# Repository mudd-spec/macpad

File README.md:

# macpad

The macpad is a 9 key macropad/keyboard with 2 EC11 style rotary encoders.

## Features:
- Sandwich style mount - 3D printable, BUT you need screws and heatset inserts
- EC11 Rotary encoders for rotational action AND they serve as switches/keys
- 9 fully programmable keys in a matrix

## CAD Model:
4 heatset inserts and 4 M3 screws are used to keep everything together

The model consists of a bottom case, a plate, and a bracket for the top, so the key switches themselves are less exposed.

There are also optional rotary encoder dials.

## PCB / Schematic
The PCB as well as the schematic is pictured below:

Schematic

PCB

## Firmware Overview
This hackpad uses [QMK](https://qmk.fm/) firmware for everything. 

- caution: the current keybinds are not advised for actual use

## BOM:
Here is everything needed to make the macpad

- 9x Cherry MX Switches
- 9x DSA Keycaps
- 4x M3x5x4 Heatset inserts
- 4X M3x12mm SHCS Bolts
- 11x 1N4148 DO-35 Diodes.
- 2x EC11 Rotary Encoder
- 1x XIAO RP2040
- 1x Case (3 3D printed parts)
- 2x Rotary Encoder Dials (2 3D printed parts)
- 1x PCB

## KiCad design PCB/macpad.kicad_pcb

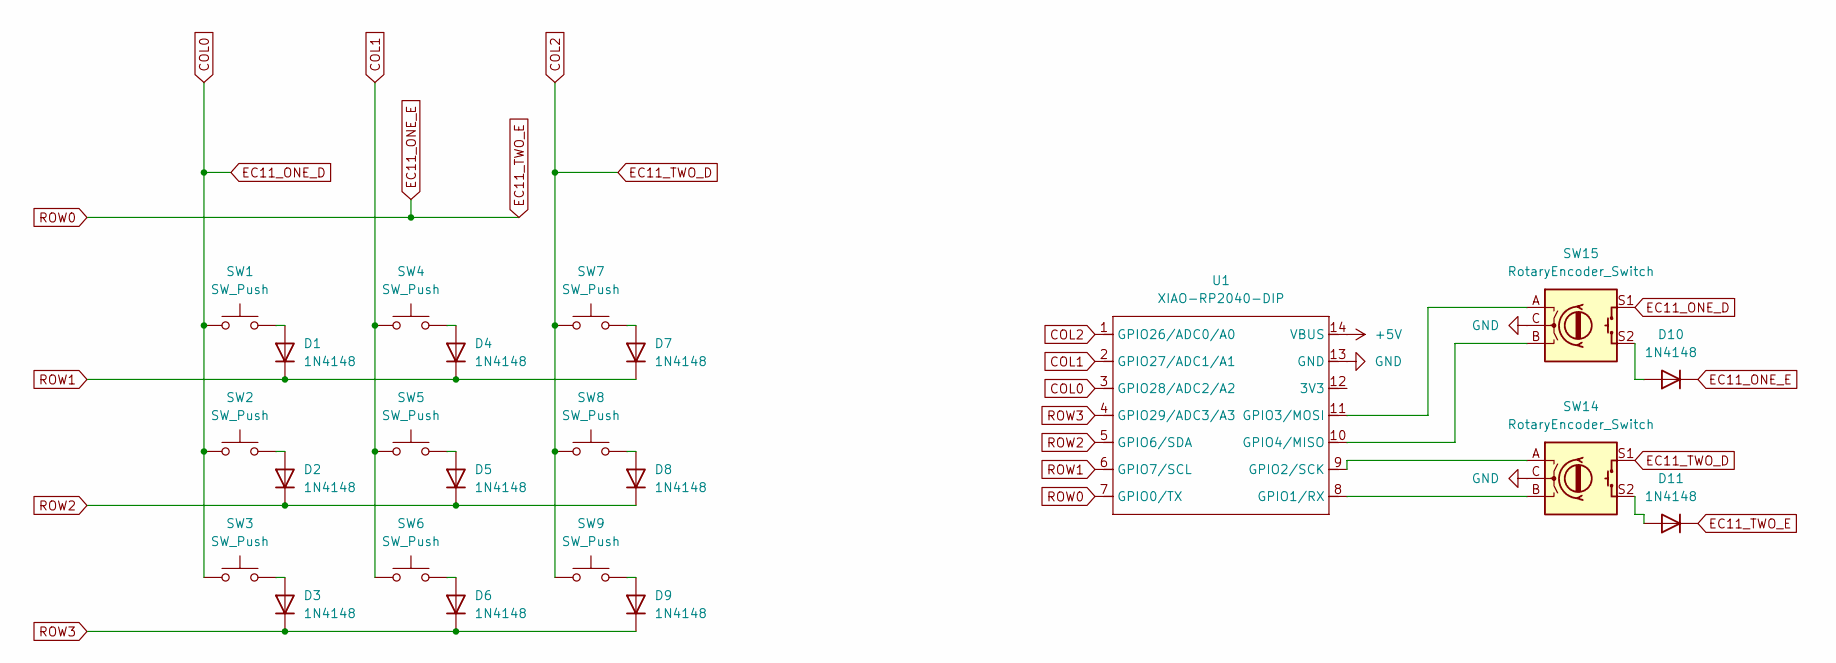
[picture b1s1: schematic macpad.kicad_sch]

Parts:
D1, D2, D3, D4, D5, D6, D7, D8, D9, D10, D11: 1N4148; D_DO-35_SOD27_P7.62mm_Horizontal
SW1, SW2, SW3, SW4, SW5, SW6, SW7, SW8, SW9: SW_Push; SW_Cherry_MX_1.00u_PCB
SW14, SW15: RotaryEncoder_Switch; RotaryEncoder_Alps_EC11E-Switch_Vertical_H20mm
U1: XIAO-RP2040-DIP

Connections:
+5V: U1.14 (VBUS)
COL0: SW1.1, SW2.1, SW3.1, SW15.S1, U1.3 (GPIO28/ADC2/A2)
COL1: SW4.1, SW5.1, SW6.1, U1.2 (GPIO27/ADC1/A1)
COL2: SW7.1, SW8.1, SW9.1, SW14.S1, U1.1 (GPIO26/ADC0/A0)
EC11_ONE_E: D10.1 (K), D11.1 (K), U1.7 (GPIO0/TX)
GND: SW14.C, SW15.C, U1.13 (GND)
unnamed: D1.2 (A), SW1.2
unnamed: D2.2 (A), SW2.2
unnamed: D3.2 (A), SW3.2
unnamed: D4.2 (A), SW4.2
unnamed: D5.2 (A), SW5.2
unnamed: D6.2 (A), SW6.2
unnamed: D7.2 (A), SW7.2
unnamed: D8.2 (A), SW8.2
unnamed: D9.2 (A), SW9.2
unnamed: D10.2 (A), SW15.S2
unnamed: D11.2 (A), SW14.S2
unnamed: SW14.B, U1.8 (GPIO1/RX)
unnamed: SW14.A, U1.9 (GPIO2/SCK)
unnamed: SW15.A, U1.11 (GPIO3/MOSI)
unnamed: SW15.B, U1.10 (GPIO4/MISO)
ROW1: D1.1 (K), D4.1 (K), D7.1 (K), U1.6 (GPIO7/SCL)
ROW2: D2.1 (K), D5.1 (K), D8.1 (K), U1.5 (GPIO6/SDA)
ROW3: D3.1 (K), D6.1 (K), D9.1 (K), U1.4 (GPIO29/ADC3/A3)

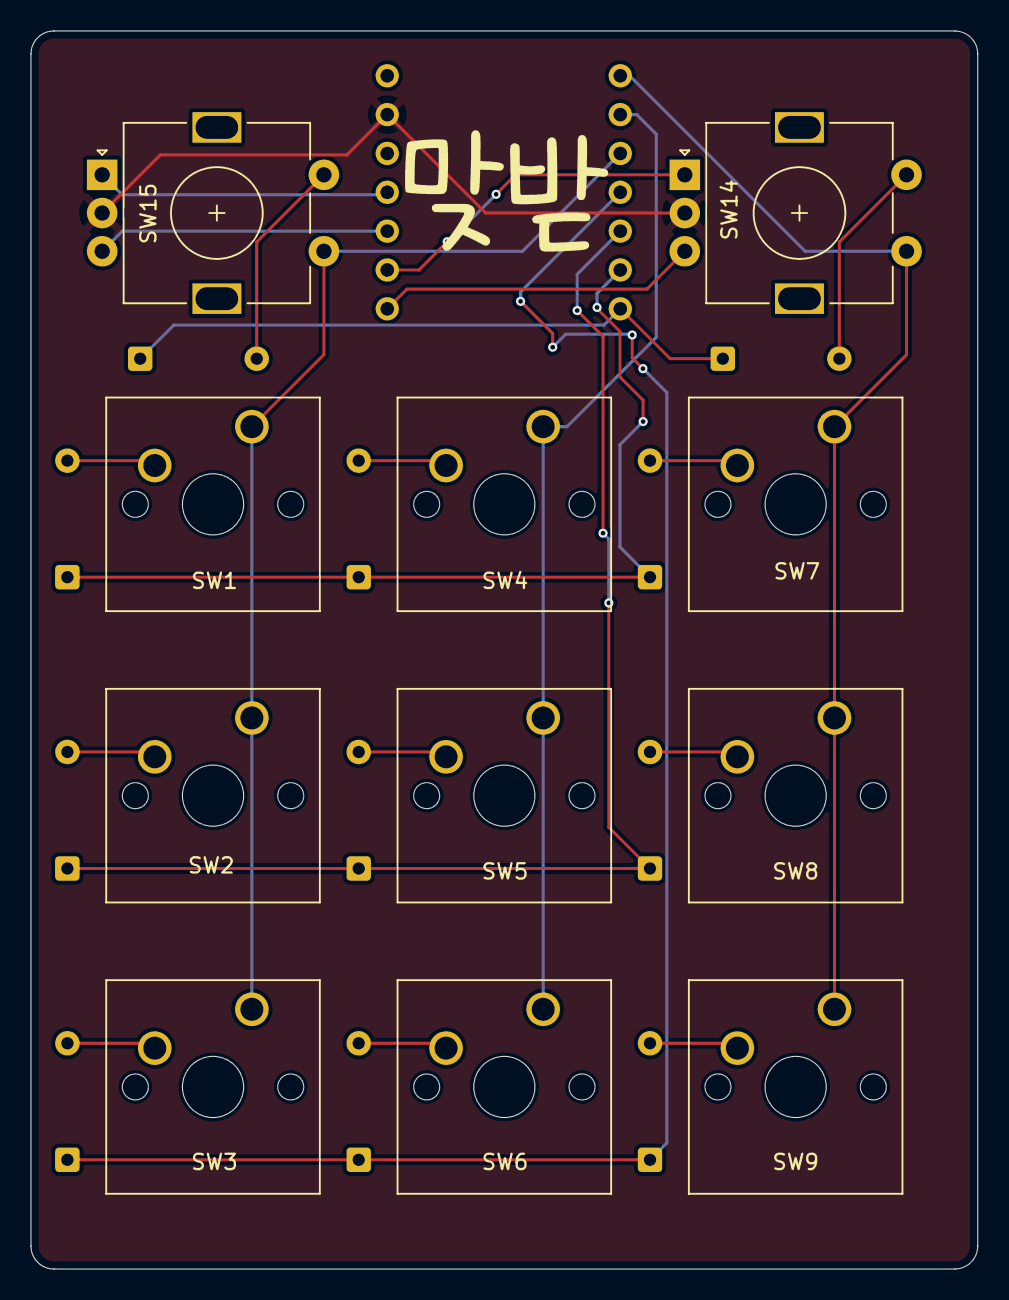
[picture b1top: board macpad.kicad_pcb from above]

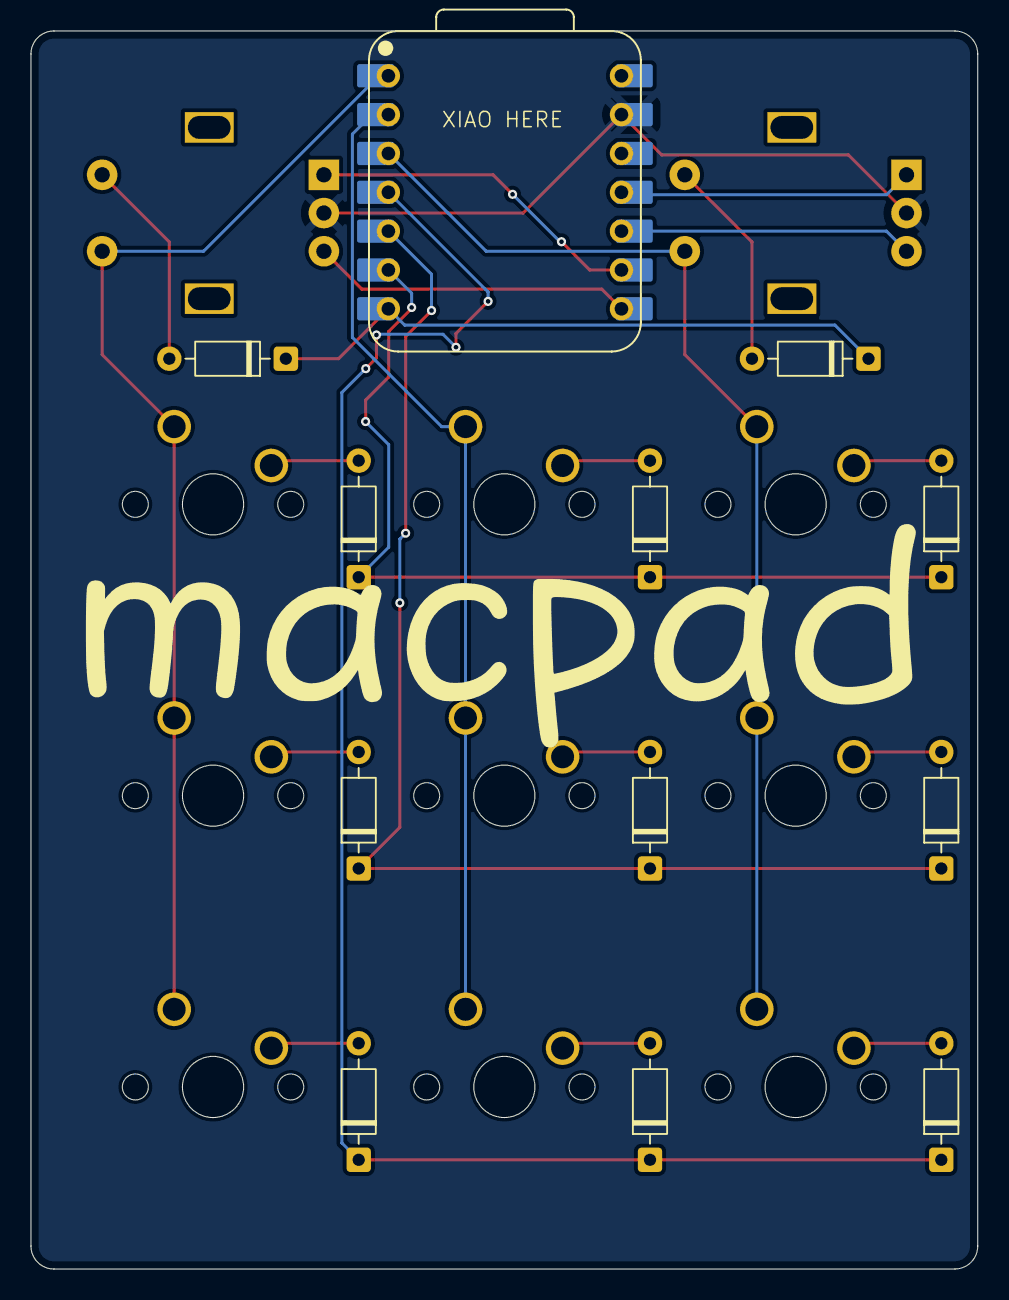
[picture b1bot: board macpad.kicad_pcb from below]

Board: 2 copper layers, 61.9 x 81.0 mm, 23 parts (12 on the bottom side), 23 nets.

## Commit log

2025-12-21 add files
2025-12-25 fix tolerances on cad
2025-12-25 fix readme and cad screw holes
2025-12-25 add silkscreen design
2025-12-28 Update README.md
    fix schematic image sizing
2025-12-30 upload step files for individual parts
